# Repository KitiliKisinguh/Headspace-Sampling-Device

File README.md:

# Heater Control System

## Headspace Sampling Device

Automatic headspace sampling is a technique used to analyze the volatile organic compounds (VOCs) present in a liquid or solid phase sample. This method utilizes heat to separate lighter, volatile compounds from a heavier matrix. Designed as a low cost and efficient solution, this project aims to provide an automated headspace sampler for use in the mass spectrometry department. It employes a closed loop microcontroller system to precisely heat a sample vial to a specific temperature using a PID controller to maintain the temperature withing a 0.1° C error margin. Once the analyte reaches equilibrium in the gas phase, it is directed to a mass spectrometer via an arrangement piping an air pump and solenoid valve. A graphical user interface (GUI) integrates these components, providing cohesive control and monitoring of the process. 

### Headspace Sampler Operation
<div align="center">
  
</div>
<p align="center">This video demonstrates the proper operation of the headspace sampling device.</p>

---

### Vial Agitation
<div align="center">
  
</div>
<p align="center">This video shows the correct technique for vial agitation during the sampling process.</p>

---

### WebServer
<div align="center">
 
</div>
<p align="center">Temperature Graph and Setpoint.</p>

---

## Control Circuits

### Interposer Board for ESP32 Controller
<div align="center">
  
</div>

**Features:**
- ESP32 microcontroller interface
- Signal conditioning
- I/O protection

---

### Heater Control PCB (KiCad Design)
<div align="center">
  
</div>

**Specifications:**
- Input: 24V DC
- Input: 5V PWM
- Output: 24V PWM
- Max current: 5A

---

### PWM Control for Inductive Loads
<div align="center">
  
</div>

**Specifications:**
- Input: 24V DC
- Input: 5V PWM
- Output: 12V PWM
- Max current: 5A

---

**File Structure**
- Fixture design files are found in 3D components folder.
- Firmware to upload to ESP32 as well as other relevant programs are found in the Code folder.
- Final Year Report, Poster and Videos are found in the Documents folder.
- Heater-Control-PCB folder conatins KiCad design files for the Heater Control PCB as well as gerber files for production.
- Interposer folder contains KiCad design files for the ESP32 interpose board and gerber files for production.
- PWM Control Folder contains KiCad design files for the PWM Controller boards for inductive loads.

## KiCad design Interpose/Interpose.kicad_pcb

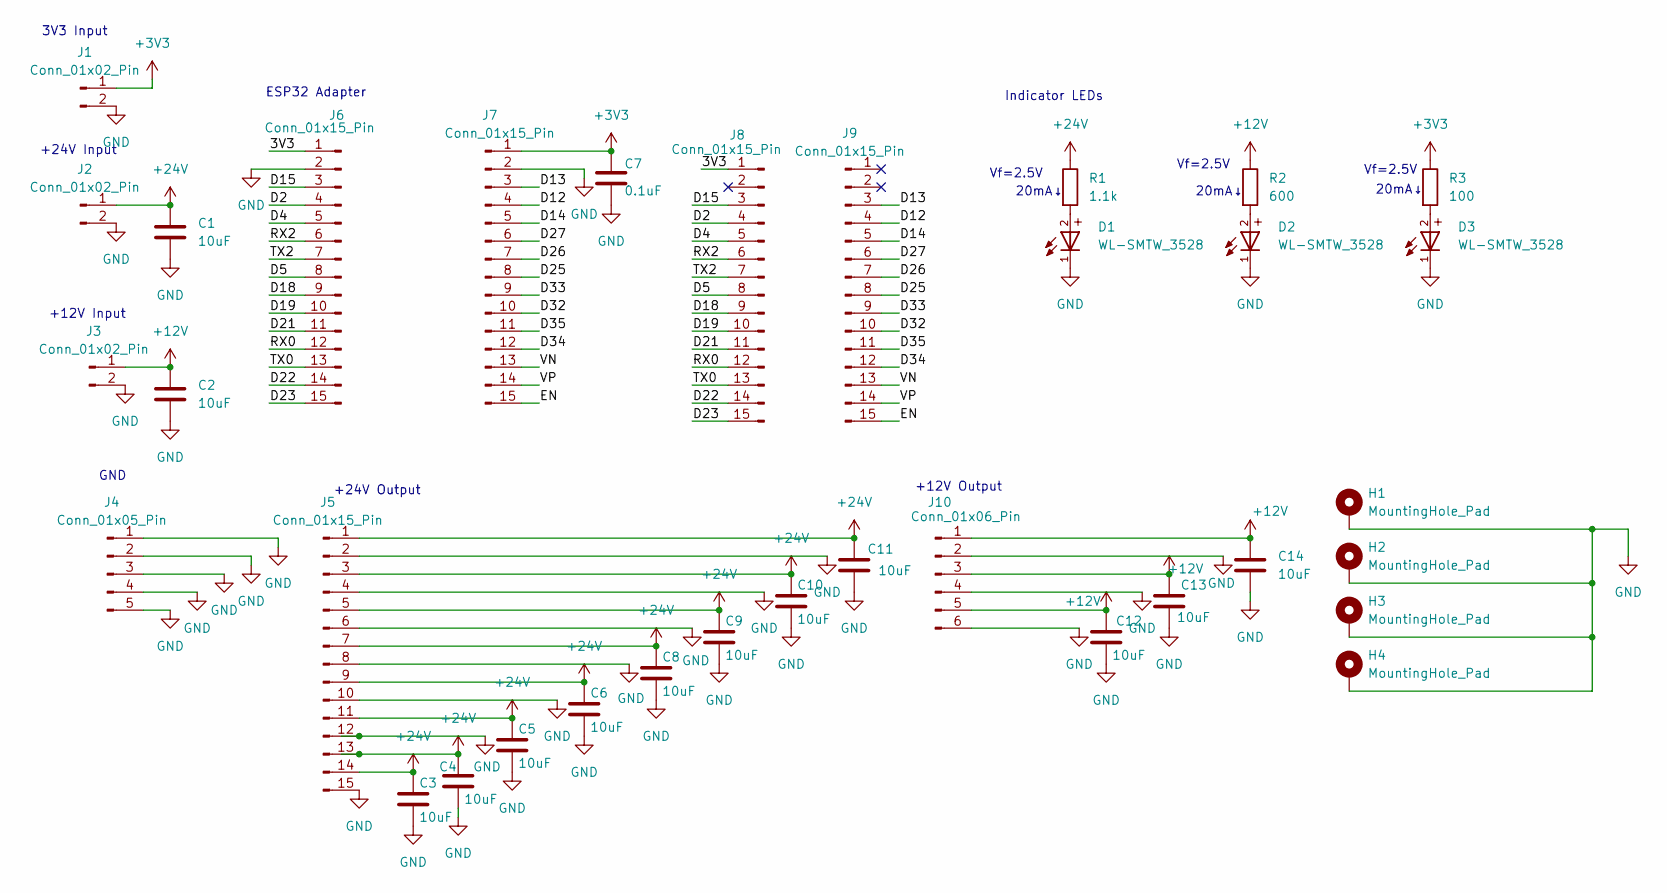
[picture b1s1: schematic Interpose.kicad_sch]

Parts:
C1, C2, C3, C4, C5, C6, C8, C9, C10, C11, C12, C13, C14: 10uF; C_1206_3216Metric
C7: 0.1uF; C_1206_3216Metric
D1, D2, D3: WL-SMTW_3528
H1, H2, H3, H4: MountingHole_Pad; MountingHole_2.2mm_M2_DIN965_Pad
J1, J2, J3: Conn_01x02_Pin; PinHeader_1x02_P2.54mm_Vertical
J4: Conn_01x05_Pin; Molex_KK-254_AE-6410-05A_1x05_P2.54mm_Vertical
J5: Conn_01x15_Pin; PinSocket_1x15_P2.54mm_Vertical
J6, J7, J8, J9: Conn_01x15_Pin; PinHeader_1x15_P2.54mm_Vertical
J10: Conn_01x06_Pin; PinHeader_1x06_P2.54mm_Vertical
R1: 1.1k; R_0402_1005Metric
R2: 600; R_0402_1005Metric
R3: 100; R_0402_1005Metric

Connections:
+3V3: C7.1, J1.1, J7.1, R3.1
+12V: C2.1, C12.1, C13.1, C14.1, J3.1, J10.1, J10.3, J10.5, R2.1
+24V: C1.1, C3.1, C4.1, C5.1, C6.1, C8.1, C9.1, C10.1, C11.1, J2.1, J5.1, J5.3, J5.5, J5.7, J5.9, J5.11, J5.13, J5.14, R1.1
/3V3: J6.1, J8.1
/D2: J6.4, J8.4
/D4: J6.5, J8.5
/D5: J6.8, J8.8
/D12: J7.4, J9.4
/D13: J7.3, J9.3
/D14: J7.5, J9.5
/D15: J6.3, J8.3
/D18: J6.9, J8.9
/D19: J6.10, J8.10
/D21: J6.11, J8.11
/D22: J6.14, J8.14
/D23: J6.15, J8.15
/D25: J7.8, J9.8
/D26: J7.7, J9.7
/D27: J7.6, J9.6
/D32: J7.10, J9.10
/D33: J7.9, J9.9
/D34: J7.12, J9.12
/D35: J7.11, J9.11
/EN: J7.15, J9.15
/RX0: J6.12, J8.12
/RX2: J6.6, J8.6
/TX0: J6.13, J8.13
/TX2: J6.7, J8.7
/VN: J7.13, J9.13
/VP: J7.14, J9.14
GND: C1.2, C2.2, C3.2, C4.2, C5.2, C6.2, C7.2, C8.2, C9.2, C10.2, C11.2, C12.2, C13.2, C14.2, D1.1, D2.1, D3.1, H1.1, H2.1, H3.1, H4.1, J1.2, J2.2, J3.2, J4.1, J4.2, J4.3, J4.4, J4.5, J5.2, J5.4, J5.6, J5.8, J5.10, J5.12, J5.15, J6.2, J7.2, J10.2, J10.4, J10.6
unnamed: D1.2, R1.2
unnamed: D2.2, R2.2
unnamed: D3.2, R3.2

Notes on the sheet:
+24V Output
3V3 Input
Vf=2.5V
+24V Input
+12V Input
+12V Output
20mA↓
Indicator LEDs
ESP32 Adapter
GND

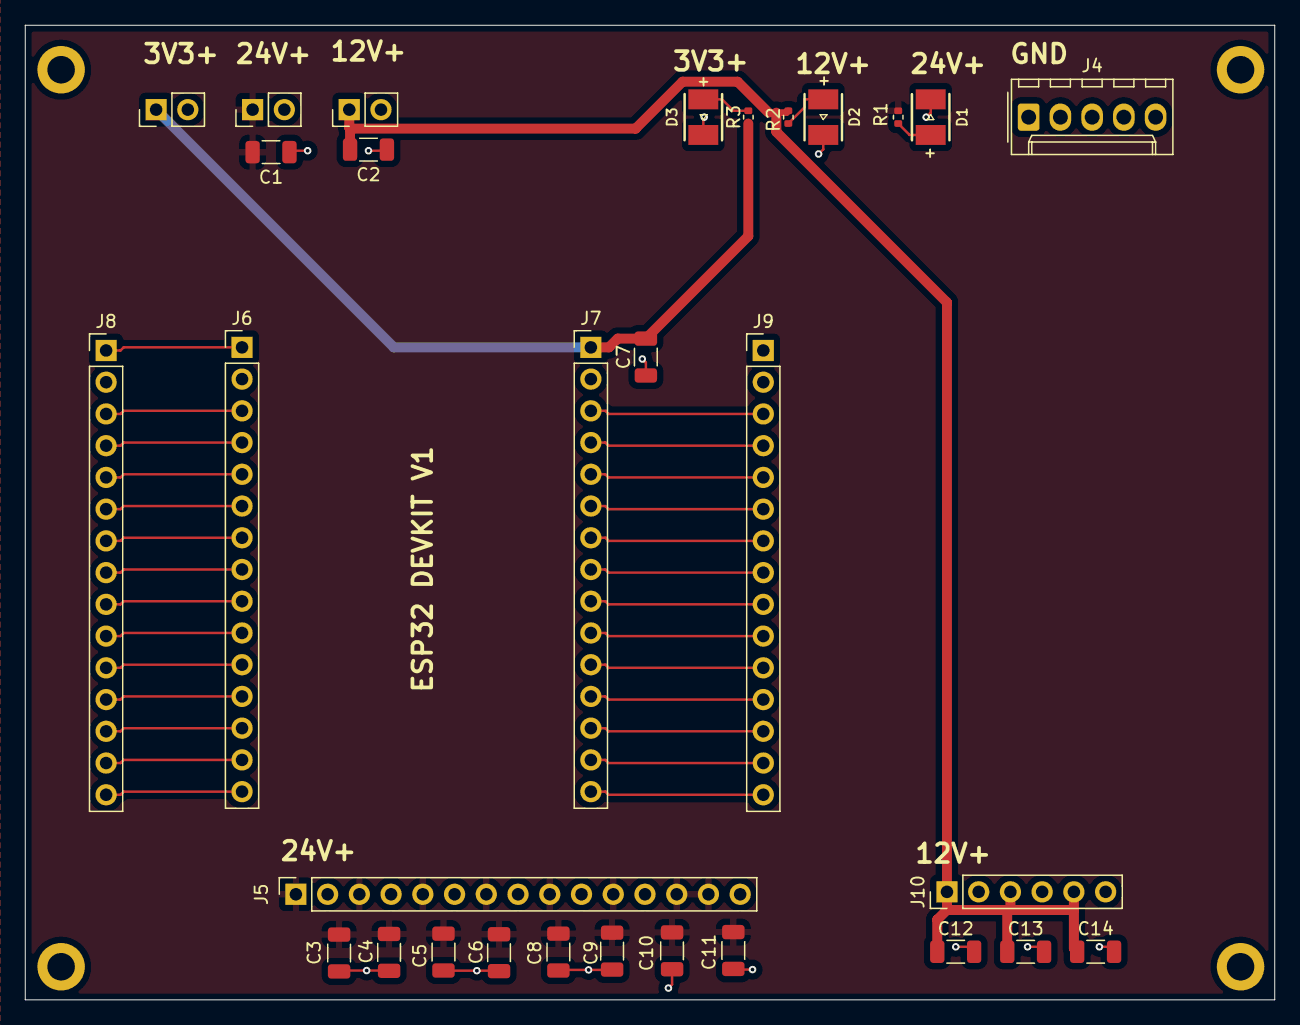
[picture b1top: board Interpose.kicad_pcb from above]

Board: 2 copper layers, 100.0 x 78.0 mm, 34 parts (0 on the bottom side), 34 nets.

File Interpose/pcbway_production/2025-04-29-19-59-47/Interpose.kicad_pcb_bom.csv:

Designator,Quantity,Value,Footprint,Package,MPN,DNP,Mount_Type,Description,MF,Description_1,Price,SnapEDA_Link,MP,Availability,Check_prices
"C1, C10, C11, C12, C13, C14, C2, C3, C4, C5, C6, C8, C9",13,10uF,C_1206_3216Metric,,,,smt,Unpolarized capacitor,,,,,,,
C7,1,0.1uF,C_1206_3216Metric,,,,smt,Unpolarized capacitor,,,,,,,
"D1, D2, D3",3,WL-SMTW_3528,WL-SMTW_3528,PLCC-2 Würth Elektronik,,,smt,,Wurth Electronics,"3528, Bright Green Typ.(@20mA): 570nm, 90mcd, 2.0V, 120° AllInGaP",None,https://www.snapeda.com/parts/150141VS73100/Wurth+Electronic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,150141VS73100,In Stock,https://www.snapeda.com/parts/150141VS73100/Wurth+Electronic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
"J1, J2, J3",3,Conn_01x02_Pin,PinHeader_1x02_P2.54mm_Vertical,,,,tht,"Generic connector, single row, 01x02, script generated",,,,,,,
J10,1,Conn_01x06_Pin,PinHeader_1x06_P2.54mm_Vertical,,,,tht,"Generic connector, single row, 01x06, script generated",,,,,,,
J4,1,Conn_01x05_Pin,Molex_KK-254_AE-6410-05A_1x05_P2.54mm_Vertical,,,,tht,"Generic connector, single row, 01x05, script generated",,,,,,,
J5,1,Conn_01x15_Pin,PinSocket_1x15_P2.54mm_Vertical,,,,tht,"Generic connector, single row, 01x15, script generated",,,,,,,
"J6, J7, J8, J9",4,Conn_01x15_Pin,PinHeader_1x15_P2.54mm_Vertical,,,,tht,"Generic connector, single row, 01x15, script generated",,,,,,,
R1,1,1.1k,R_0402_1005Metric,,,,smt,Resistor,,,,,,,
R2,1,600,R_0402_1005Metric,,,,smt,Resistor,,,,,,,
R3,1,100,R_0402_1005Metric,,,,smt,Resistor,,,,,,,

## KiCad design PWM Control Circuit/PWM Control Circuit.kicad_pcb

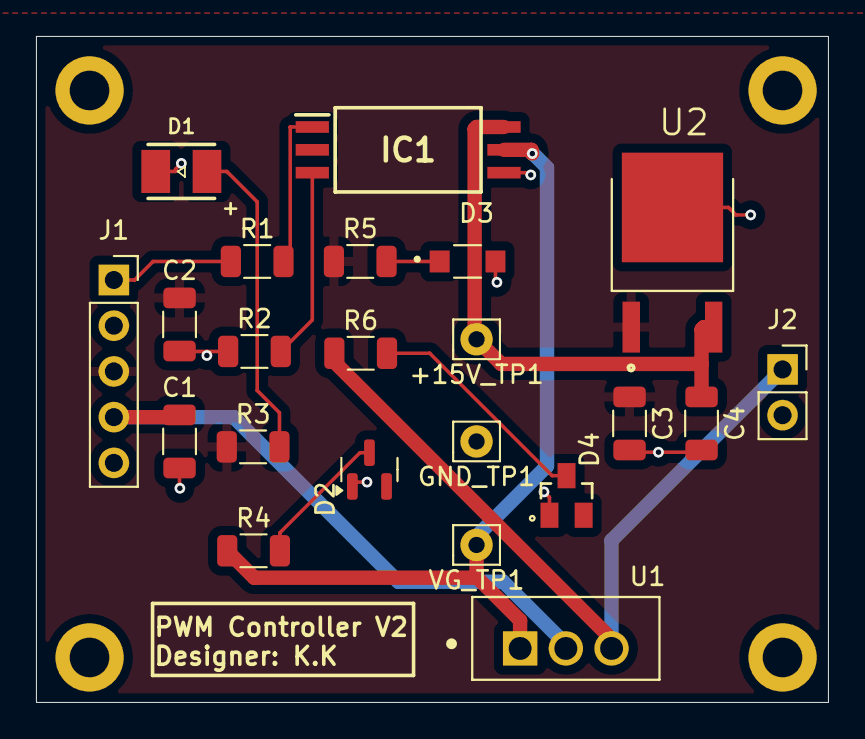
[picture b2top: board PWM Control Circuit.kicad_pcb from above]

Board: 2 copper layers, 44.0 x 37.0 mm, 26 parts (0 on the bottom side), 13 nets.

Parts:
+15V_TP1: TestPoint; Pin_D0.9mm_L10.0mm_W2.4mm_FlatFork
C1, C2, C4: 10uF; C_1206_3216Metric
C3: 0.33uF; C_1206_3216Metric
D1: KA-3528SGT; WL-SMTW_3528
D2: BZX84C15; SOT-23
D3: BZD27C24P R3G; SODFL3618X143N
D4: PMEG3005ET-QR; SOT23
GND_TP1: TestPoint; Pin_D0.9mm_L10.0mm_W2.4mm_FlatFork
H1, H2, H3, H4: MountingHole_Pad_MP; MountingHole_2.2mm_M2_DIN965_Pad
IC1: UCC23513QDWYRQ1; SOIC127P1150X355-6N
J1: Conn_01x05_Pin; PinSocket_1x05_P2.54mm_Vertical
J2: Conn_01x02_Pin; PinSocket_1x02_P2.54mm_Vertical
R1, R2: 130R; R_1206_3216Metric
R3, R5: 1.1k; R_1206_3216Metric
R4: 15k; R_1206_3216Metric
R6: 2.4k; R_1206_3216Metric
U1: STP55NF06L; TO254P1040X460X1935-3
U2: MC7815CDTRKG; DPAK229P990X238-4N
VG_TP1: TestPoint; Pin_D0.9mm_L10.0mm_W2.4mm_FlatFork

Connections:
+12V: C1.1, J1.4, U1.2
+24V: C2.1, C3.1, J1.3, R3.1, R5.1, U2.1 (IN)
/+15V: +15V_TP1.1, C4.1, IC1.6 (VCC), U2.3 (OUT)
/PWM input: J1.1, R1.1
/VG: IC1.5 (VOUT), R4.1, U1.1, VG_TP1.1
/Vsource: J2.1, R6.1, U1.3
GND: C1.2, C2.2, C3.2, C4.2, D1.1, D2.1 (A), D3.2, D4.1, GND_TP1.1, IC1.4 (VEE), J1.2, J1.5, J2.2, R2.1, U2.2 (GND)
unnamed: D1.2, R3.2
unnamed: D2.3 (K), R4.2
unnamed: D3.1, R5.2
unnamed: D4.3, R6.2
unnamed: IC1.1 (ANODE), R1.2
unnamed: IC1.3 (CATHODE), R2.2

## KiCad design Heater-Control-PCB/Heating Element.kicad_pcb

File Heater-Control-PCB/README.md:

# Heater-Control-PCB

**Heater Control PCB using KiCad**  
Designed to regulate PWM from 24V to 12V

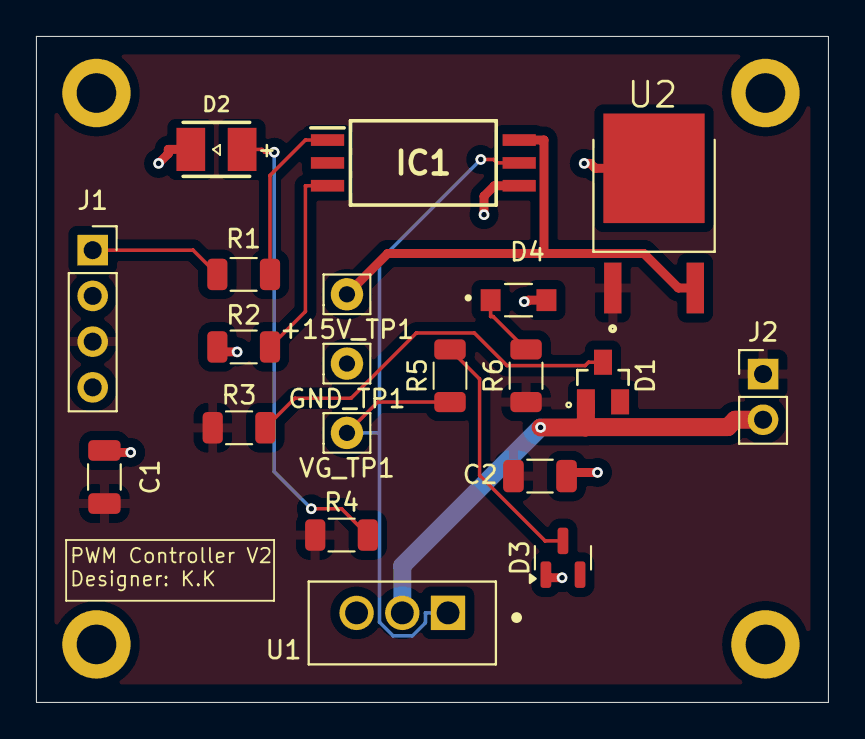
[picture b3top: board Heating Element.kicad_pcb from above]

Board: 2 copper layers, 44.0 x 37.0 mm, 24 parts (0 on the bottom side), 12 nets.

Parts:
+15V_TP1: TestPoint; Pin_D0.9mm_L10.0mm_W2.4mm_FlatFork
C1: 0.1uF; C_1206_3216Metric
C2: 0.33uF; C_1206_3216Metric
D1: PMEG3005ET-QR; SOT23
D2: KA-3528SGT; WL-SMTW_3528
D3: BZX84C15; SOT-23
D4: BZD27C24P R3G; SODFL3618X143N
GND_TP1: TestPoint; Pin_D0.9mm_L10.0mm_W2.4mm_FlatFork
H1, H2, H3, H4: MountingHole_Pad_MP; MountingHole_2.2mm_M2_DIN965_Pad
IC1: UCC23513QDWYRQ1; SOIC127P1150X355-6N
J1: Conn_01x04_Pin; PinSocket_1x04_P2.54mm_Vertical
J2: Conn_01x02_Pin; PinHeader_1x02_P2.54mm_Vertical
R1, R2: 130R; R_1206_3216Metric
R3: 2.4k; R_1206_3216Metric
R4, R6: 1.1k; R_1206_3216Metric
R5: 15k; R_1206_3216Metric
U1: STP55NF06L; TO254P1040X460X1935-3
U2: MC7815CDTRKG; DPAK229P990X238-4N
VG_TP1: TestPoint; Pin_D0.9mm_L10.0mm_W2.4mm_FlatFork

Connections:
+24V: C1.1, C2.1, J1.3, J2.1, R3.1, R4.1, R6.1, U2.1 (IN)
/+15V: +15V_TP1.1, IC1.6 (VCC), U2.3 (OUT)
/PWM input: J1.1, R1.1
/VG: IC1.5 (VOUT), R5.1, U1.1, VG_TP1.1
/Vdrain: D1.1, J2.2, U1.2
GND: C1.2, C2.2, D2.1, D3.1 (A), D4.2, GND_TP1.1, IC1.4 (VEE), J1.2, J1.4, R2.1, U1.3, U2.2 (GND)
unnamed: D1.3, R3.2
unnamed: D2.2, R4.2
unnamed: D3.3 (K), R5.2
unnamed: D4.1, R6.2
unnamed: IC1.1 (ANODE), R1.2
unnamed: IC1.3 (CATHODE), R2.2

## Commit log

2024-11-14 Intital Commit
2024-11-14 updated PCB to have bezels
2024-11-29 Updated schematic and PCB
2024-12-04 Updated Schematic components (all smd) Updated PCB layout (includes schematic changes and routing) Updtaed Gerber files
2024-12-04 Added latest pcbway production files
2024-12-04 Components and 3D models
2025-05-24 updated Heating PCB
2025-05-24 Added image folder and updated README
2025-05-24 Updated file structure
2025-05-25 Added ESP32 Interpose & PWM control Circuit
2025-05-25 Added Images, Videos, Report and updated Readme
2025-05-25 updated Videos
2025-05-25 updated Readme and added poster
2025-05-25 ReadMe
2025-05-25 Updared ReadMe
2025-05-25 fixed Vial Agitation gif
2025-05-25 updated Vial Agitation gif
2025-05-26 Added 3D components folder and Code
2025-05-27 Fixed Code folder Error and adjusted vial agitation gif width
2025-05-27 updated Readme, and added Images to Documents folder
2025-05-27 removed redundant files in the code folder and updated Readme
2025-05-27 added preoject description to Readme and updated report.pdf
